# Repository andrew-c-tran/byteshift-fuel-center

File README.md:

# ByteShift Fuel Center

An automotive CAN module that reads fuel pressure, fuel temperature and ethanol content and puts them on the
bus at 100 Hz.

- **Sensors:** GM 13577429 flex fuel sensor (ethanol %, fuel temperature) and Honeywell MIP 0-150 psi
  pressure sensor (EFI Hardware H-PS150G-HMIP).
- **Output:** CAN 500 kbit/s, ID 0x5A6 every 10 ms, CRC-8 and rolling counter in every frame.
- **Fails safe:** any fault reports 0 % ethanol and 0 kPa *and* sets an error flag, so a broken sensor or wire
  can never look like high ethanol or present pressure.
- **Hardware:** NXP S32K116, AEC-qualified parts throughout, sealed Deutsch DT 12-way connector,
  JLCPCB-ready fabrication and assembly files.

Rev A boards have been manufactured and verified.

## Design rules

1. **Automotive-grade, every part.** Fuel matters and the engine bay is hostile. Aftermarket boards commonly use
   commercial or industrial parts rated to 70 or 85 °C. Every electronic part on this board is AEC-qualified, the
   same standard carmakers require: AEC-Q100 ICs, AEC-Q101 discretes and AEC-Q200 passives, all rated for at least
   −40 to 125 °C. The connector is a sealed Deutsch DT.
2. **Fail safe.** Every fault fails toward low ethanol and no pressure, and is flagged. Every frame carries a
   CRC-8 and a rolling counter so the receiver can reject bad frames and detect a dead module.
3. **Ready to order.** Every part must be in stock at JLCPCB when the design is updated; an exotic part helps
   no one. Download, upload to JLCPCB, order. `python3 hardware/check_stock.py` checks current stock.

## Documentation

| | |
|---|---|
| [docs/protocol.md](docs/protocol.md) | CAN frames, CRC-8, configuration |
| [docs/hardware.md](docs/hardware.md) | Schematic overview, pinouts, ordering, installation |
| [docs/firmware.md](docs/firmware.md) | Build, test, flash |
| [docs/sensors.md](docs/sensors.md) | Sensor wiring, signals and fault behaviour |

## Quick start

```sh
make -C firmware test          # host unit tests
make -C firmware/s32k116       # target firmware (Arm GNU toolchain)
python3 hardware/check_stock.py 50   # JLCPCB stock for 50 boards
```

To order boards, follow [docs/hardware.md#ordering](docs/hardware.md#ordering).

Open `hardware/kicad/fuel-center.kicad_pro` in KiCad 8 or later.

## Disclaimer

This module feeds data to engine management. Validate it on your own vehicle and use it at your own risk.

## License

Copyright (C) 2026 ByteShift Labs LLC

- Firmware and documentation: [GPL-3.0-or-later](LICENSE)
- Hardware (`hardware/`): [CERN-OHL-S-2.0](hardware/LICENSE)

Third-party files keep their own terms: NXP device support in `firmware/s32k116/nxp/`
([BSD-3-Clause](firmware/s32k116/nxp/LICENSE)) and the component library in `hardware/lib/` (see its
[README](hardware/lib/README.md)).

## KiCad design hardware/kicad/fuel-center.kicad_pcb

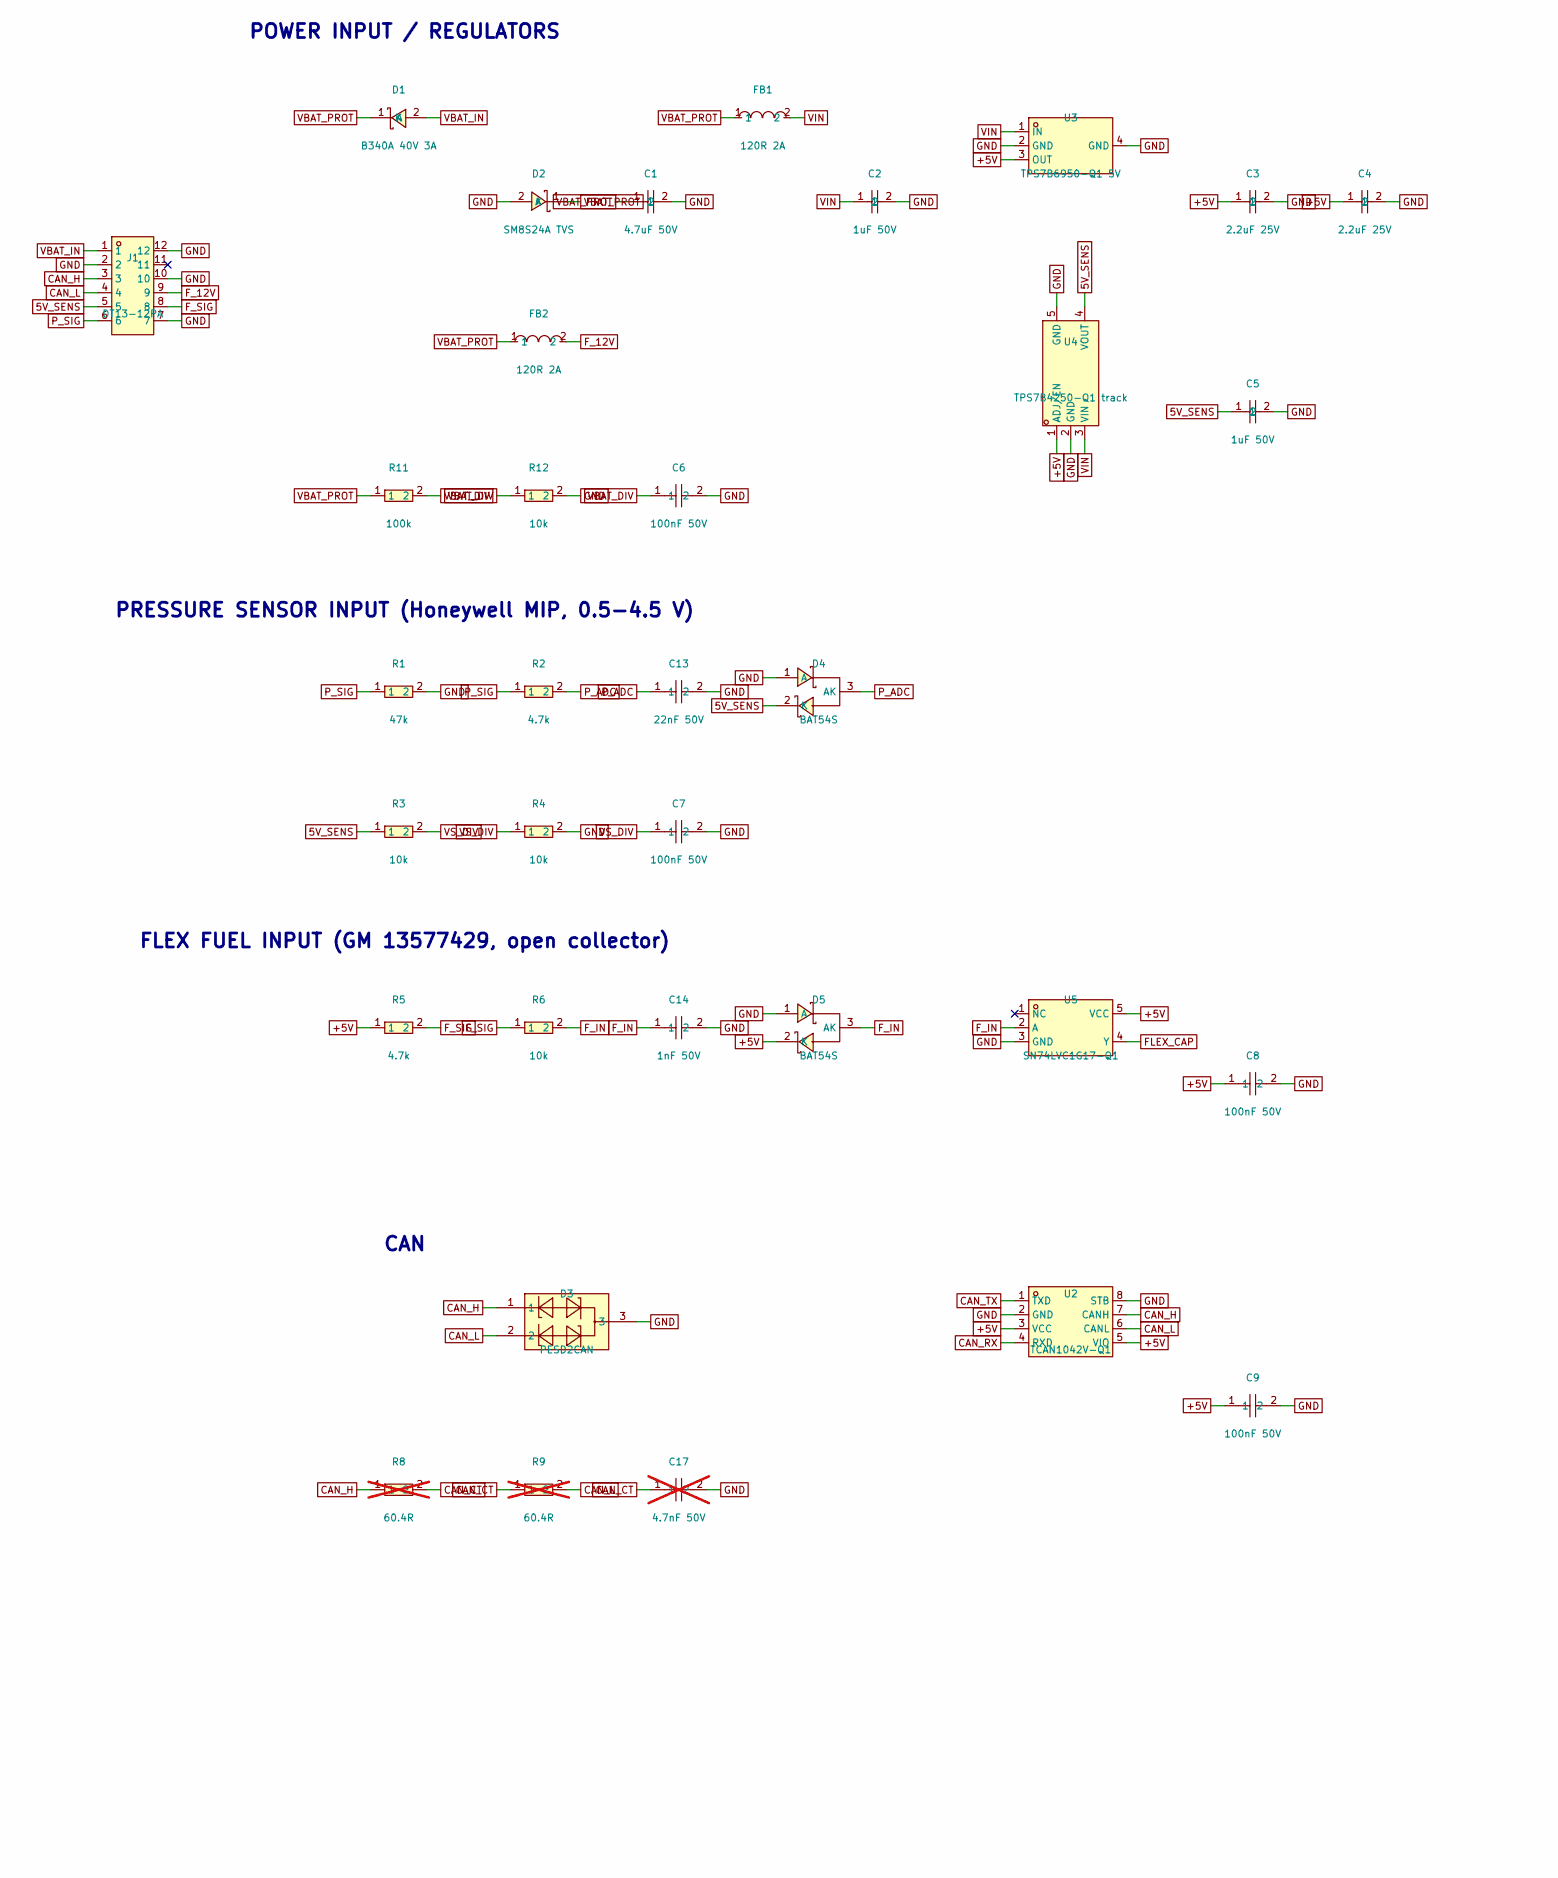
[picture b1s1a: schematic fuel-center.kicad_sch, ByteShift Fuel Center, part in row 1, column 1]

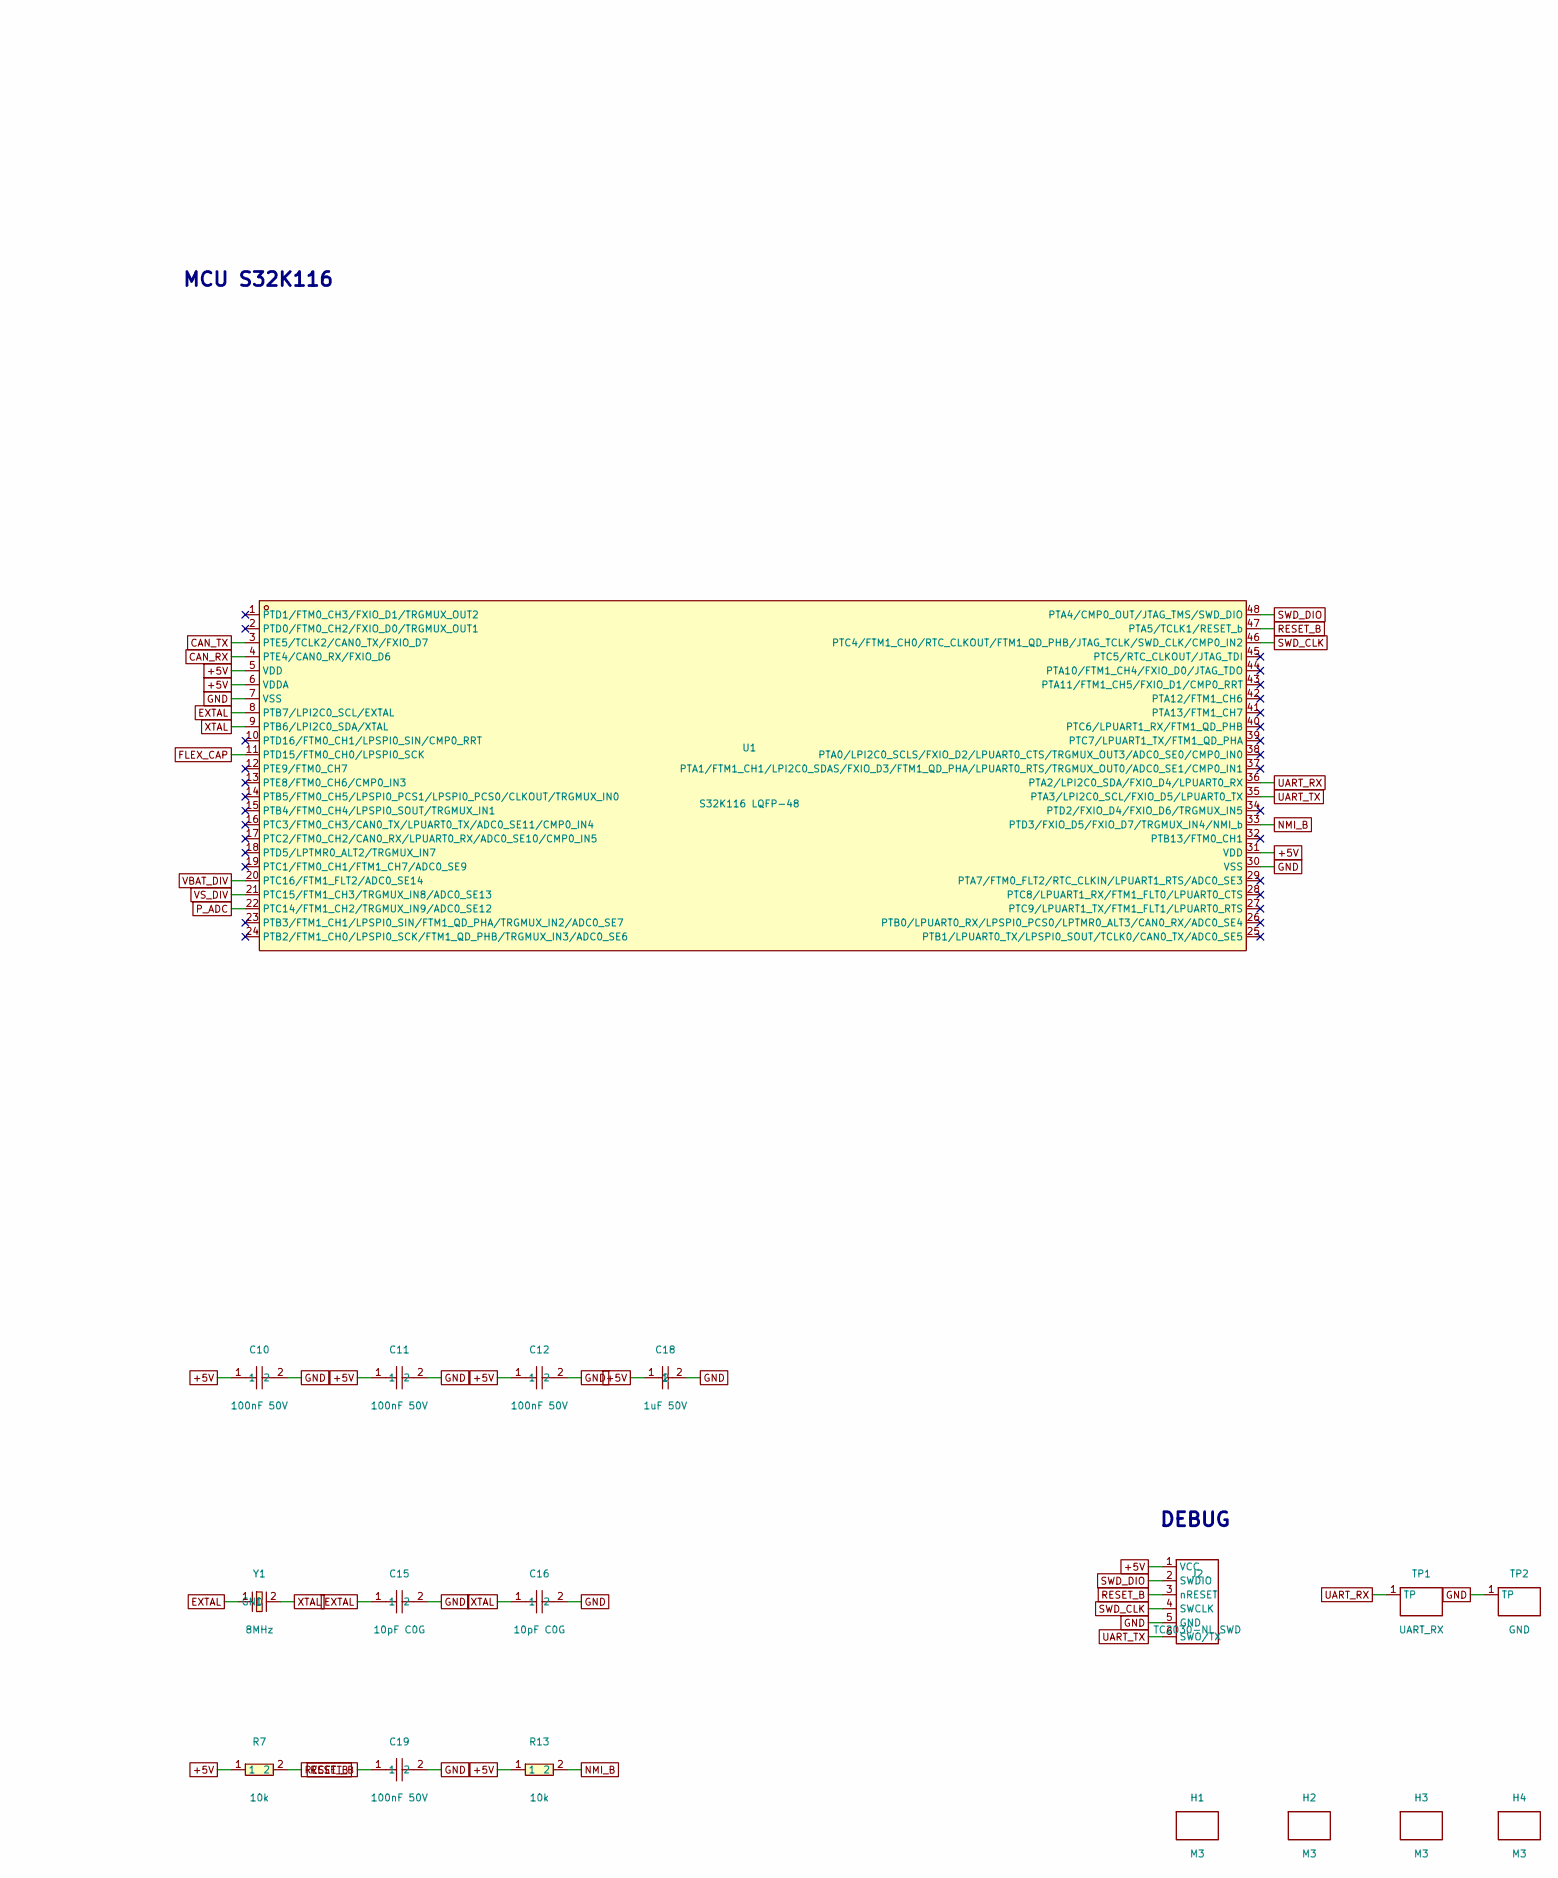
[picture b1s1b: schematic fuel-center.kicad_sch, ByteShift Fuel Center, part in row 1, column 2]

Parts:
C1: 4.7uF 50V; C1206; MPN CGA5L1X7R1H475KT0Y0S; LCSC C412300
C2, C5, C18: 1uF 50V; C0805; MPN GCM21BR71H105KA03L; LCSC C126592
C3, C4: 2.2uF 25V; C0805; MPN GCM21BR71E225KA73L; LCSC C126591
C6, C7, C8, C9, C10, C11, C12, C19: 100nF 50V; C0603; MPN CGA3E2X7R1H104KT0Y0N; LCSC C76711
C13: 22nF 50V; C0603; MPN GCM188R71H223KA37J; LCSC C3838411
C14: 1nF 50V; C0603; MPN CL10B102KB8WPNC; LCSC C307344
C15, C16: 10pF C0G; C0603; MPN GCM1885C2A100JA16D; LCSC C126575
C17: 4.7nF 50V; C0603; MPN GCM188R71H472KA37D; LCSC C161228; not fitted
D1: B340A 40V 3A; SMA_L4.4-W2.6-LS5.0-RD; MPN B340A-13-F; LCSC C85098
D2: SM8S24A TVS; DO-218AB_L13.5-W8.4-LS15.5-FD; MPN SM8S24A; LCSC C314439
D3: PESD2CAN; SOT-23-3_L2.9-W1.3-P1.90-LS2.4-BR; MPN PESD2CAN,215; LCSC C75176
D4, D5: BAT54S; SOT-23-3_L3.0-W1.7-P0.95-LS2.9-BR; MPN BAT54S-QR; LCSC C7507573
FB1, FB2: 120R 2A; L0603; MPN BLM18PG121SH1D; LCSC C354394
H1, H2, H3, H4: M3; MOUNTHOLE
J1: DT13-12PA; CONN-TH_DT13-12PA_C6423578; MPN DT13-12PA; LCSC C6423578
J2: TC2030-NL SWD; TC2030
R1: 47k; R0603; MPN AC0603FR-0747KL; LCSC C111134
R2, R5: 4.7k; R0603; MPN AC0603FR-074K7L; LCSC C116697
R3, R4, R6, R7, R12, R13: 10k; R0603; MPN AC0603FR-0710KL; LCSC C116677
R8, R9: 60.4R; R0603; MPN CRCW060360R4FKEA; LCSC C844801; not fitted
R11: 100k; R0603; MPN AC0603FR-07100KL; LCSC C116674
TP1: UART_RX; TESTPOINT
TP2: GND; TESTPOINT
U1: S32K116 LQFP-48; LQFP-48_L7.0-W7.0-P0.50-LS9.0-BL; MPN FS32K116LFT0MLFT; LCSC C1137392
U2: TCAN1042V-Q1; SOIC-8_L4.9-W3.9-P1.27-LS6.0-BL; MPN TCAN1042VDRQ1; LCSC C485806
U3: TPS7B6950-Q1 5V; SOT-223-4_L6.5-W3.5-P2.30-LS7.0-BR; MPN TPS7B6950QDCYRQ1; LCSC C108469
U4: TPS7B4250-Q1 track; SOT-23-5_L3.0-W1.7-P0.95-LS2.8-BL; MPN TPS7B4250QDBVRQ1; LCSC C188757
U5: SN74LVC1G17-Q1; SC-70-5_L2.1-W1.3-P0.65-LS2.1-BL; MPN SN74LVC1G17QDCKRQ1; LCSC C205900
Y1: 8MHz; OSC-SMD_2P-L3.2-W2.5; MPN NX3225GD-8MHZ-STD-CRA-3; LCSC C889706

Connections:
5V_SENS: C5.1, D4.2 (K), J1.5, R3.1, U4.4 (VOUT)
+5V: C3.1, C4.1, C8.1, C9.1, C10.1, C11.1, C12.1, C18.1, D5.2 (K), J2.1 (VCC), R5.1, R7.1, R13.1, U1.5 (VDD), U1.6 (VDDA), U1.31 (VDD), U2.3 (VCC), U2.5 (VIO), U3.3 (OUT), U4.1 (ADJ/EN), U5.5 (VCC)
CAN_CT: C17.1, R8.2, R9.1
CAN_H: D3.1, J1.3, R8.1, U2.7 (CANH)
CAN_L: D3.2, J1.4, R9.2, U2.6 (CANL)
CAN_RX: U1.4 (PTE4/CAN0_RX/FXIO_D6), U2.4 (RXD)
CAN_TX: U1.3 (PTE5/TCLK2/CAN0_TX/FXIO_D7), U2.1 (TXD)
EXTAL: C15.1, U1.8 (PTB7/LPI2C0_SCL/EXTAL), Y1.1
FLEX_CAP: U1.11 (PTD15/FTM0_CH0/LPSPI0_SCK), U5.4 (Y)
F_12V: FB2.2, J1.9
F_IN: C14.1, D5.3 (AK), R6.2, U5.2 (A)
F_SIG: J1.8, R5.2, R6.1
GND: C1.2, C2.2, C3.2, C4.2, C5.2, C6.2, C7.2, C8.2, C9.2, C10.2, C11.2, C12.2, C13.2, C14.2, C15.2, C16.2, C17.2, C18.2, C19.2, D2.2 (A), D3.3, D4.1 (A), D5.1 (A), J1.2, J1.7, J1.10, J1.12, J2.5 (GND), R1.2, R4.2, R12.2, TP2.1, U1.7 (VSS), U1.30 (VSS), U2.2 (GND), U2.8 (STB), U3.2 (GND), U3.4 (GND), U4.2 (GND), U4.5 (GND), U5.3 (GND)
NMI_B: R13.2, U1.33 (PTD3/FXIO_D5/FXIO_D7/TRGMUX_IN4/NMI_b)
P_ADC: C13.1, D4.3 (AK), R2.2, U1.22 (PTC14/FTM1_CH2/TRGMUX_IN9/ADC0_SE12)
P_SIG: J1.6, R1.1, R2.1
RESET_B: C19.1, J2.3 (nRESET), R7.2, U1.47 (PTA5/TCLK1/RESET_b)
SWD_CLK: J2.4 (SWCLK), U1.46 (PTC4/FTM1_CH0/RTC_CLKOUT/FTM1_QD_PHB/JT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)
SWD_DIO: J2.2 (SWDIO), U1.48 (PTA4/CMP0_OUT/JTAG_TMS/SWD_DIO)
UART_RX: TP1.1, U1.36 (PTA2/LPI2C0_SDA/FXIO_D4/LPUART0_RX)
UART_TX: J2.6 (SWO/TX), U1.35 (PTA3/LPI2C0_SCL/FXIO_D5/LPUART0_TX)
VBAT_DIV: C6.1, R11.2, R12.1, U1.20 (PTC16/FTM1_FLT2/ADC0_SE14)
VBAT_IN: D1.2 (A), J1.1
VBAT_PROT: C1.1, D1.1 (K), D2.1 (K), FB1.1, FB2.1, R11.1
VIN: C2.1, FB1.2, U3.1 (IN), U4.3 (VIN)
VS_DIV: C7.1, R3.2, R4.1, U1.21 (PTC15/FTM1_CH3/TRGMUX_IN8/ADC0_SE13)
XTAL: C16.1, U1.9 (PTB6/LPI2C0_SDA/XTAL), Y1.2 (GND)

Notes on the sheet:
POWER INPUT / REGULATORS
PRESSURE SENSOR INPUT (Honeywell MIP, 0.5-4.5 V)
FLEX FUEL INPUT (GM 13577429, open collector)
CAN
MCU S32K116
DEBUG

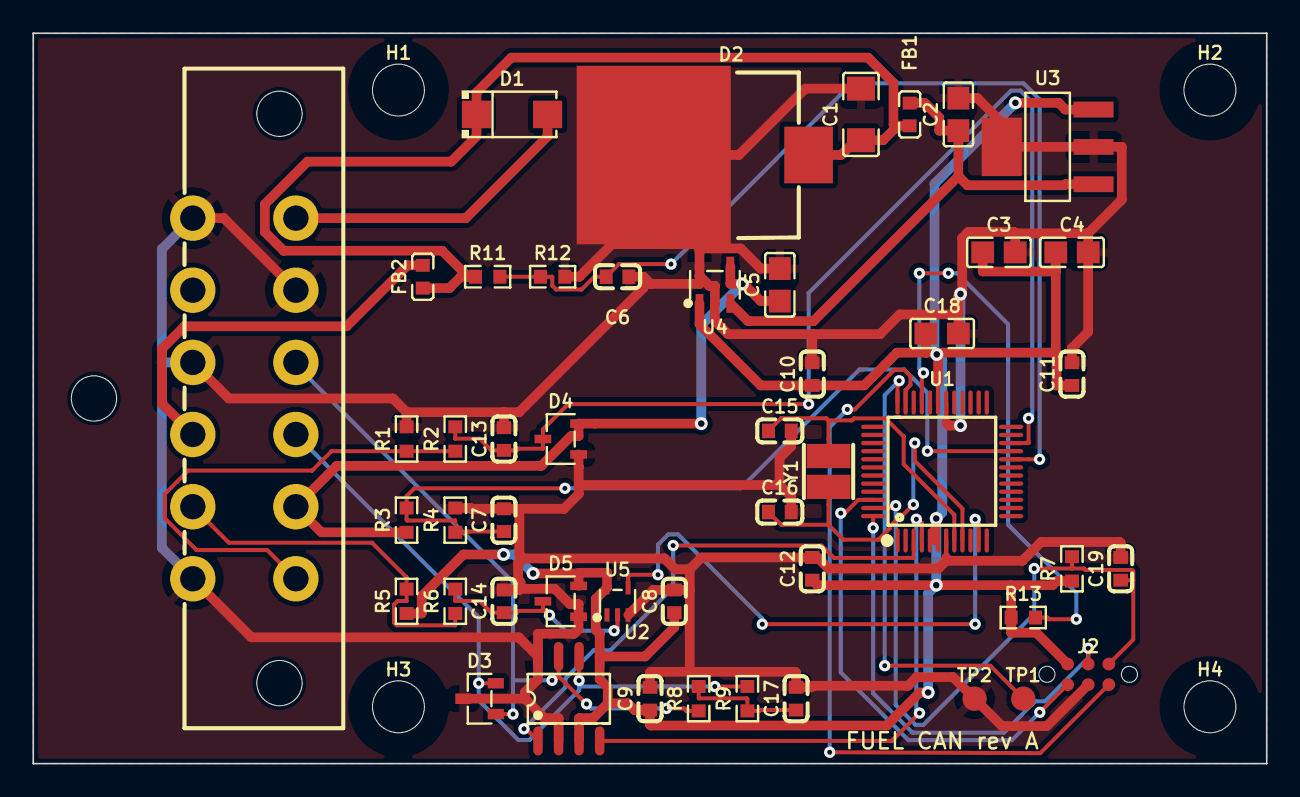
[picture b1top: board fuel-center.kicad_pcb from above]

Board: 2 copper layers, 76.0 x 45.0 mm, 52 parts (0 on the bottom side), 27 nets.

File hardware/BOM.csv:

Refs,Qty,Value,MPN,LCSC,Qualification,DNP,Notes
C1,1,4.7uF 50V,CGA5L1X7R1H475KT0Y0S,C412300,AEC-Q200 (TDK CGA),,input bulk; keep >5 mm from board edge/holes (flex cracking). Alt Samsung CL31B475KBHVPNE C307372
"C2,C5,C18",3,1uF 50V,GCM21BR71H105KA03L,C126592,AEC-Q200 (Murata GCM),,
"C3,C4",2,2.2uF 25V,GCM21BR71E225KA73L,C126591,AEC-Q200 (Murata GCM),,
"C6,C7,C8,C9,C10,C11,C12,C19",8,100nF 50V,CGA3E2X7R1H104KT0Y0N,C76711,AEC-Q200 (TDK CGA),,
C13,1,22nF 50V,GCM188R71H223KA37J,C3838411,AEC-Q200 (Murata GCM),,
C14,1,1nF 50V,CL10B102KB8WPNC,C307344,AEC-Q200 (Samsung P-code),,
"C15,C16",2,10pF C0G,GCM1885C2A100JA16D,C126575,AEC-Q200 Rev D (Murata datasheet GCM1885C2A100JA16-01A),,crystal load; alt Samsung CL10C100JB81PNC C307356
C17,1,4.7nF 50V,GCM188R71H472KA37D,C161228,AEC-Q200 (Murata GCM),DNP,split termination centre
D1,1,B340A 40V 3A,B340A-13-F,C85098,AEC-Q101 (LCSC page),,reverse polarity
D2,1,SM8S24A TVS,SM8S24A,C314439,AEC-Q101 ISO7637-2 (LCSC page),,load dump TVS; alt BORN C151945
D3,1,PESD2CAN,"PESD2CAN,215",C75176,AEC-Q101 (LCSC page),,CAN ESD
"D4,D5",2,BAT54S,BAT54S-QR,C7507573,AEC-Q101 (Nexperia BAT54S-Q datasheet),,NOT the plain BAT54S (not AEC-Q101)
"FB1,FB2",2,120R 2A,BLM18PG121SH1D,C354394,"AEC-Q200 (Murata H1D, Newark listing)",,flex sensor 12 V feed
J1,1,DT13-12PA,DT13-12PA,C6423578,TE Deutsch IP68 (outside AEC-Q200 scope),,"mating plug DT06-12SA + W12S wedge; if JLC stock is short, add it through JLC Global Sourcing (Mouser/DigiKey stock it)"
J2,1,TC2030-NL SWD,,,n/a,,"TC2030-NL tag-connect pads, no part"
R1,1,47k,AC0603FR-0747KL,C111134,AEC-Q200 (Yageo AC),,
"R2,R5",2,4.7k,AC0603FR-074K7L,C116697,AEC-Q200 (Yageo AC),,
"R8,R9",2,60.4R,CRCW060360R4FKEA,C844801,AEC-Q200 (Vishay CRCW),DNP,split termination; fit only if this node ends the bus
R11,1,100k,AC0603FR-07100KL,C116674,AEC-Q200 (Yageo AC),,
"R12,R3,R4,R6,R7,R13",6,10k,AC0603FR-0710KL,C116677,AEC-Q200 (Yageo AC),,
TP1,1,UART_RX,,,n/a,,test pad
TP2,1,GND,,,n/a,,test pad
U1,1,S32K116 LQFP-48,FS32K116LFT0MLFT,C1137392,AEC-Q100 G1 (NXP family page),,run at 5 V; alt FS32K116LFT0MLFR C1850160 (same part on reel)
U2,1,TCAN1042V-Q1,TCAN1042VDRQ1,C485806,AEC-Q100 G1 (LCSC page),,alt TJA1042T/3/1J C132227
U3,1,TPS7B6950-Q1 5V,TPS7B6950QDCYRQ1,C108469,AEC-Q100 G1 (LCSC page),,5 V 150 mA SOT-223; stable with 2x2.2 uF ceramic; no reverse protection (D1 provides it)
U4,1,TPS7B4250-Q1 track,TPS7B4250QDBVRQ1,C188757,AEC-Q100 (TI -Q1),,tracking LDO for sensor 5 V; short-circuit protected
U5,1,SN74LVC1G17-Q1,SN74LVC1G17QDCKRQ1,C205900,AEC-Q100 (LCSC page),,Schmitt buffer on flex input
Y1,1,8MHz,NX3225GD-8MHZ-STD-CRA-3,C889706,AEC-Q200 (NDK catalog),,8 pF load; the 10 pF load caps assume ~3 pF stray

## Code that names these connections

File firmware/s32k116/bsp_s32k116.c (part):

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 * Copyright (C) 2026 ByteShift Labs LLC */
/* Board support for the fuel CAN module on NXP S32K116 LQFP-48 at 5 V.
 * Clocks: FIRC 48 MHz core / 24 MHz bus; SOSC 8 MHz crystal feeds FTM0 (1 MHz timestamps) and FlexCAN (500 kbit/s).
 * Pins: PTE4/PTE5 CAN0, PTD15 FTM0_CH0 (flex), PTC14/15/16 ADC0_SE12/13/14 (P_ADC, VS_DIV, VBAT_DIV), PTA2/3 LPUART0. */
#include "S32K116.h"
#include "S32K116_features.h"
#include "bsp.h"
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

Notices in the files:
firmware/s32k116/bsp_s32k116.c:
SPDX-License-Identifier: GPL-3.0-or-later
hardware/kicad/fuel-center.kicad_sch:
Copyright (C) 2026 ByteShift Labs LLC. Licensed under CERN-OHL-S-2.0
